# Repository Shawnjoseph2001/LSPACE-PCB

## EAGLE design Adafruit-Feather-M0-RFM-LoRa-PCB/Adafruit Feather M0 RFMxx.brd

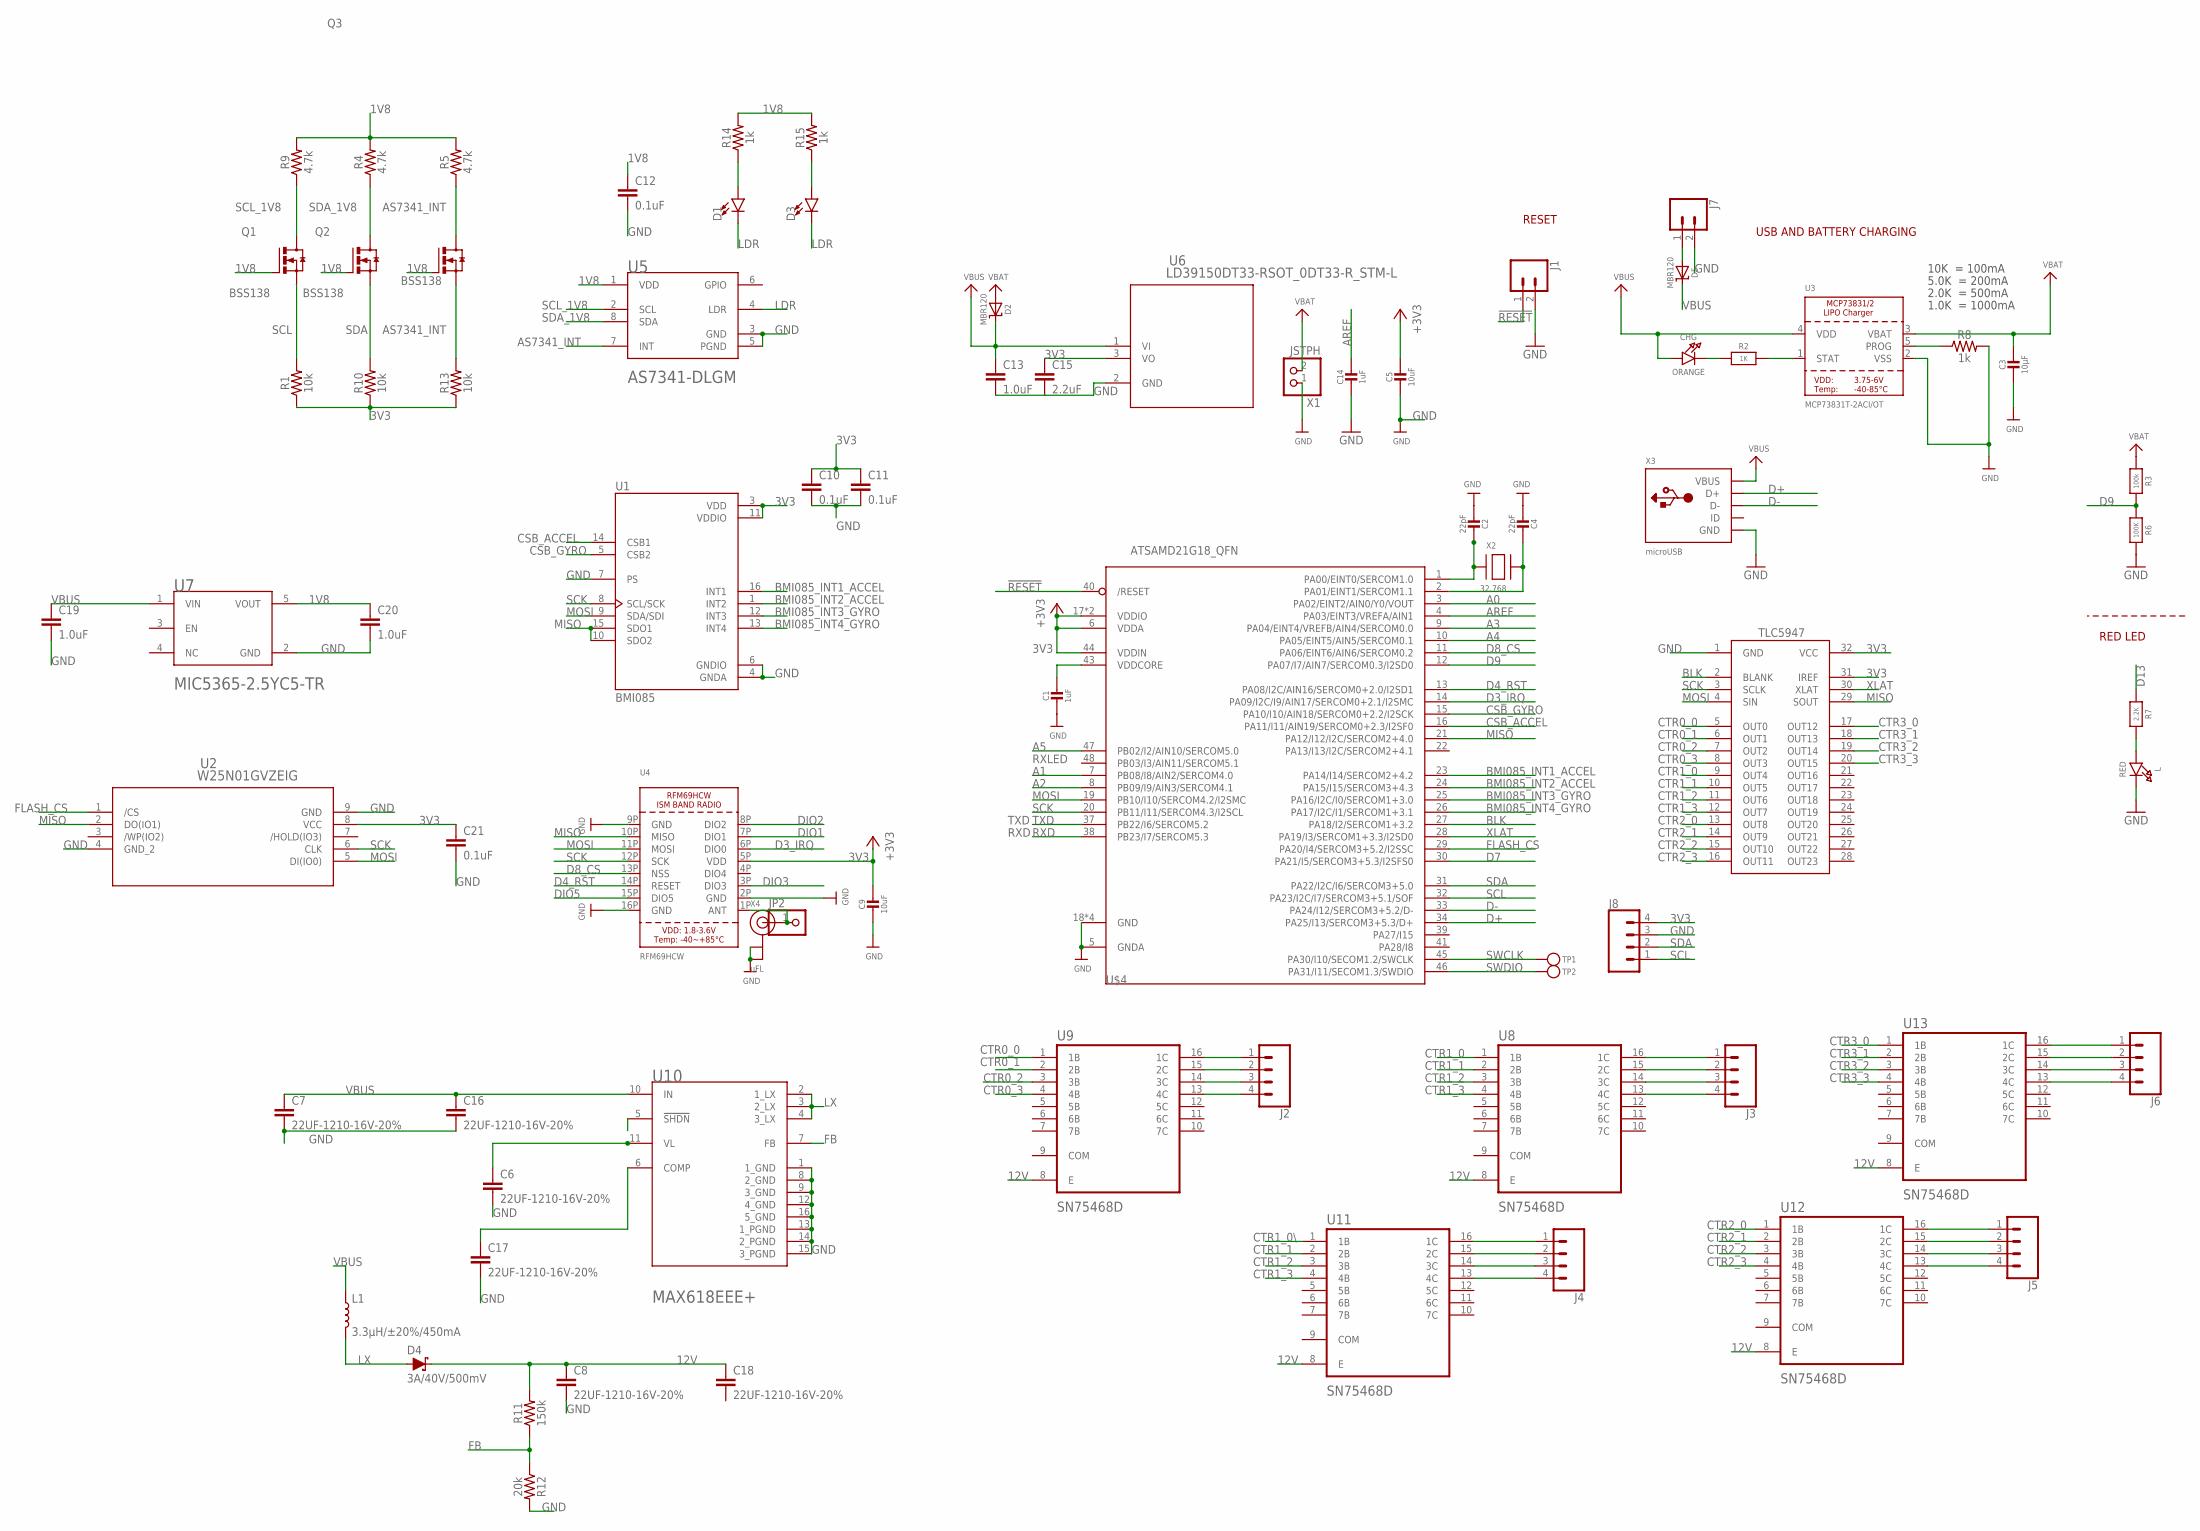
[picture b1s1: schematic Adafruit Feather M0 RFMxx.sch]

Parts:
C1, C14: 1uF; 0603-NO
C2, C4: 22pF; 0603-NO
C3: 10µF; 0805-NO
C5, C9: 10uF; 0805-NO
C6, C7, C8, C16, C17, C18: 22UF-1210-16V-20%; 1210
C10, C11, C12, C21: 0.1uF; 0603
C13, C19, C20: 1.0uF; 0805
C15: 2.2uF; 0805
CHG: ORANGE; CHIPLED_0805_NOOUTLINE
D1, D3: LED1206; LED-1206
D2, D5: MBR120; SOD-123
D4: 3A/40V/500mV; SMA-DIODE
IC1: TLC5947-DAP; HTSSOP32DAP
J1, J7: CONN_02; 1X02
J2, J3, J4, J5, J6, J8: CONN_04; 1X04
JP2: HEADER-1X1ROUND; 1X01_ROUND
L: RED; CHIPLED_0805_NOOUTLINE
L1: 3.3µH/±20%/450mA; 0805
Q1, Q2, Q3: BSS138; SOT23-3
R1, R10, R13: 10k; 0603
R2: 1K; 0603-NO
R3: 100k; 0603-NO
R4, R5, R9: 4.7k; 0603
R6: 100K; 0603-NO
R7: 2.2K; 0603-NO
R8, R14, R15: 1k; 0603
R11: 150k; 0603
R12: 20k; 0603
TP1, TP2: TESTPOINTROUND1.5MM; TESTPOINT_ROUND_1.5MM
U1: BMI085; PQFN50P450X300X100-16N
U2: W25N01GVZEIG; WSON-8_6X5_WIN
U3: MCP73831T-2ACI/OT; SOT23-5
U4: RFM69HCW; RFMHCW_SMT
U5: AMS_AS7341-DLGMAMS_AS7341-DLGM_0_0; AMS_AS7341-DLGM_0
U6: LD39150DT33-RSOT_0DT33-R_STM-L; SOT_0DT33-R_STM-L
U7: MICROCHIP_MIC5365-2_5YC5-TRMICROCHIP_MIC5365-2_5Y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; MICROCHIP_MIC5365-2_5YC5-TR_0
U8, U9, U11, U12, U13: SN75468D; SOIC127P600X175-16N
U10: MAXIM_MAX618EEE+MAXIM_MAX618EEE+_0_0; MAXIM_MAX618EEE+_0
U$4: ATSAMD21G18_QFN; TQFN48_7MM
X1: JSTPH; JSTPH2
X2: 32.768; XTAL3215
X3: microUSB; 4UCONN_20329_V2
X4: uFL; U.FL

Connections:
1V8: C12.1, C20.1, Q1.1 (G), Q2.1 (G), Q3.1 (G), R4.2, R5.2, R9.2, R14.2, R15.2, U5.1 (VDD), U7.5 (VOUT)
3V3: C5.1, C9.1, C10.1, C11.1, C15.1, C21.1, IC1.31 (IREF), IC1.32 (VCC), J8.4, R1.1, R10.1, R13.1, U1.3 (VDD), U1.11 (VDDIO), U2.8 (VCC), U4.5P (VDD), U6.3 (VO), U$4.6 (VDDA), U$4.17 (VDDIO), U$4.36 (VDDIO), U$4.44 (VDDIN)
12V: C8.1, C18.1, D4.C, R11.2, U8.8 (E), U9.8 (E), U11.8 (E), U12.8 (E), U13.8 (E)
!RESET: J1.1, U$4.40 (/RESET)
A0: U$4.3 (PA02/EINT2/AIN0/Y0/VOUT)
A1: U$4.7 (PB08/I8/AIN2/SERCOM4.0)
A2: U$4.8 (PB09/I9/AIN3/SERCOM4.1)
A3: U$4.9 (PA04/EINT4/VREFB/AIN4/SERCOM0.0)
A4: U$4.10 (PA05/EINT5/AIN5/SERCOM0.1)
A5: U$4.47 (PB02/I2/AIN10/SERCOM5.0)
ANT: JP2.1, U4.1P (ANT), X4.3 (SIGNAL)
AREF: C14.1, U$4.4 (PA03/EINT3/VREFA/AIN1)
AS7341_INT: Q3.2 (S), Q3.3 (D), R5.1, R13.2, U5.7 (INT)
BLK: IC1.2 (BLANK), U$4.27 (PA18/I2/SERCOM1+3.2)
BMI085_INT1_ACCEL: U1.16 (INT1), U$4.23 (PA14/I14/SERCOM2+4.2)
BMI085_INT2_ACCEL: U1.1 (INT2), U$4.24 (PA15/I15/SERCOM3+4.3)
BMI085_INT3_GYRO: U1.12 (INT3), U$4.25 (PA16/I2C/I0/SERCOM1+3.0)
BMI085_INT4_GYRO: U1.13 (INT4), U$4.26 (PA17/I2C/I1/SERCOM1+3.1)
CSB_ACCEL: U1.14 (CSB1), U$4.16 (PA11/I11/AIN19/SERCOM0+2.3/I2SF0)
CSB_GYRO: U1.5 (CSB2), U$4.15 (PA10/I10/AIN18/SERCOM0+2.2/I2SCK)
CTR0_0: IC1.5 (OUT0), U9.1 (1B)
CTR0_1: IC1.6 (OUT1), U9.2 (2B)
CTR0_2: IC1.7 (OUT2), U9.3 (3B)
CTR0_3: IC1.8 (OUT3), U9.4 (4B)
CTR1_0: IC1.9 (OUT4), U8.1 (1B)
CTR1_0\: U11.1 (1B)
CTR1_1: IC1.10 (OUT5), U8.2 (2B), U11.2 (2B)
CTR1_2: IC1.11 (OUT6), U8.3 (3B), U11.3 (3B)
CTR1_3: IC1.12 (OUT7), U8.4 (4B), U11.4 (4B)
CTR2_0: IC1.13 (OUT8), U12.1 (1B)
CTR2_1: IC1.14 (OUT9), U12.2 (2B)
CTR2_2: IC1.15 (OUT10), U12.3 (3B)
CTR2_3: IC1.16 (OUT11), U12.4 (4B)
CTR3_0: IC1.17 (OUT12), U13.1 (1B)
CTR3_1: IC1.18 (OUT13), U13.2 (2B)
CTR3_2: IC1.19 (OUT14), U13.3 (3B)
CTR3_3: IC1.20 (OUT15), U13.4 (4B)
D3_IRQ: U4.6P (DIO0), U$4.14 (PA09/I2C/I9/AIN17/SERCOM0+2.1/I2SMC)
D4_RST: U4.14P (RESET), U$4.13 (PA08/I2C/AIN16/SERCOM0+2.0/I2SD1)
D7: U$4.30 (PA21/I5/SERCOM3+5.3/I2SFS0)
D8_CS: U4.13P (NSS), U$4.11 (PA06/EINT6/AIN6/SERCOM0.2)
D9: R3.2, R6.1, U$4.12 (PA07/I7/AIN7/SERCOM0.3/I2SD0)
D13: R7.1
D+: U$4.34 (PA25/I13/SERCOM3+5.3/D+), X3.D+
D-: U$4.33 (PA24/I12/SERCOM3+5.2/D-), X3.D-
DIO1: U4.7P (DIO1)
DIO2: U4.8P (DIO2)
DIO3: U4.3P (DIO3)
DIO5: U4.15P (DIO5)
FB: R11.1, R12.1, U10.7 (FB)
FLASH_CS: U2.1 (/CS), U$4.29 (PA20/I4/SERCOM3+5.2/I2SSC)
GND: C1.2, C2.2, C3.2, C4.2, C5.2, C6.2, C7.2, C8.2, C9.2, C10.2, C11.2, C12.2, C13.2, C14.2, C15.2, C16.2, C17.2, C19.2, C20.2, C21.2, IC1.1 (GND), J1.2, J7.2, J8.3, L.C, R6.2, R8.2, R12.2, U1.4 (GNDA), U1.6 (GNDIO), U1.7 (PS), U2.4 (GND_2), U2.9 (GND), U3.2 (VSS), U4.2P (GND), U4.9P (GND), U4.16P (GND), U5.3 (GND), U5.5 (PGND), U6.2 (GND), U7.2 (GND), U10.1 (1_GND), U10.8 (2_GND), U10.9 (3_GND), U10.12 (4_GND), U10.13 (1_PGND), U10.14 (2_PGND), U10.15 (3_PGND), U10.16 (5_GND), U$4.5 (GNDA), U$4.18 (GND), U$4.35 (GND), U$4.42 (GND), U$4.THERMAL (GND), X1.1, X3.BASE@1 (GND), X3.BASE@2 (GND), X3.GND, X3.SPRT@1 (GND), X3.SPRT@2 (GND), X3.SPRT@3 (GND), X3.SPRT@4 (GND), X4.1 (GND), X4.2 (GND)
LDR: D1.C, D3.C, U5.4 (LDR)
LX: D4.A, L1.2, U10.2 (1_LX), U10.3 (2_LX), U10.4 (3_LX)
MISO: IC1.29 (SOUT), U1.10 (SDO2), U1.15 (SDO1), U2.2 (DO(IO1)), U4.10P (MISO), U$4.21 (PA12/I12/I2C/SERCOM2+4.0)
MOSI: IC1.4 (SIN), U1.9 (SDA/SDI), U2.5 (DI(IO0)), U4.11P (MOSI), U$4.19 (PB10/I10/SERCOM4.2/I2SMC)
unnamed: CHG.C, R2.1
unnamed: L.A, R7.2
unnamed: R2.2, U3.1 (STAT)
unnamed: R8.1, U3.5 (PROG)
unnamed: C2.1, U$4.1 (PA00/EINT0/SERCOM1.0), X2.P$1
unnamed: D1.A, R14.1
unnamed: C4.1, U$4.2 (PA01/EINT1/SERCOM1.1), X2.P$2
unnamed: D3.A, R15.1
unnamed: C6.1, U10.11 (VL)
unnamed: C17.1, U10.6 (COMP)
unnamed: J3.1, U8.16 (1C)
unnamed: J3.2, U8.15 (2C)
unnamed: J3.3, U8.14 (3C)
unnamed: J3.4, U8.13 (4C)
unnamed: J2.1, U9.16 (1C)
unnamed: J2.2, U9.15 (2C)
unnamed: J2.3, U9.14 (3C)
unnamed: J2.4, U9.13 (4C)
unnamed: J4.1, U11.16 (1C)
unnamed: J4.2, U11.15 (2C)
unnamed: J4.3, U11.14 (3C)
unnamed: J4.4, U11.13 (4C)
unnamed: J5.1, U12.16 (1C)
unnamed: J5.2, U12.15 (2C)
unnamed: J5.3, U12.14 (3C)
unnamed: J5.4, U12.13 (4C)
unnamed: J6.1, U13.16 (1C)
unnamed: J6.2, U13.15 (2C)
unnamed: J6.3, U13.14 (3C)
unnamed: J6.4, U13.13 (4C)
unnamed: D5.A, J7.1
RXD: U$4.38 (PB23/I7/SERCOM5.3)
SCK: IC1.3 (SCLK), U1.8 (SCL/SCK), U2.6 (CLK), U4.12P (SCK), U$4.20 (PB11/I11/SERCOM4.3/I2SCL)
SCL: J8.1, Q1.2 (S), R1.2, U$4.32 (PA23/I2C/I7/SERCOM3+5.1/SOF)
SCL_1V8: Q1.3 (D), R9.1, U5.2 (SCL)
SDA: J8.2, Q2.2 (S), R10.2, U$4.31 (PA22/I2C/I6/SERCOM3+5.0)
SDA_1V8: Q2.3 (D), R4.1, U5.8 (SDA)
SWCLK: TP1.P$1, U$4.45 (PA30/I10/SECOM1.2/SWCLK)
SWDIO: TP2.P$1, U$4.46 (PA31/I11/SECOM1.3/SWDIO)
TXD: U$4.37 (PB22/I6/SERCOM5.2)
VBAT: C3.1, D2.A, R3.1, U3.3 (VBAT), X1.2
VBUS: C7.1, C13.1, C16.1, C19.1, CHG.A, D2.C, D5.C, L1.1, U3.4 (VDD), U6.1 (VI), U7.1 (VIN), U10.10 (IN), X3.VBUS
VDDCORE: C1.1, U$4.43 (VDDCORE)
XLAT: IC1.30 (XLAT), U$4.28 (PA19/I3/SERCOM1+3.3/I2SD0)

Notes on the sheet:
RESET
10K = 100mA
5.0K = 200mA
2.0K = 500mA
1.0K = 1000mA
RXLED
TXD
RXD
USB AND BATTERY CHARGING
RED LED

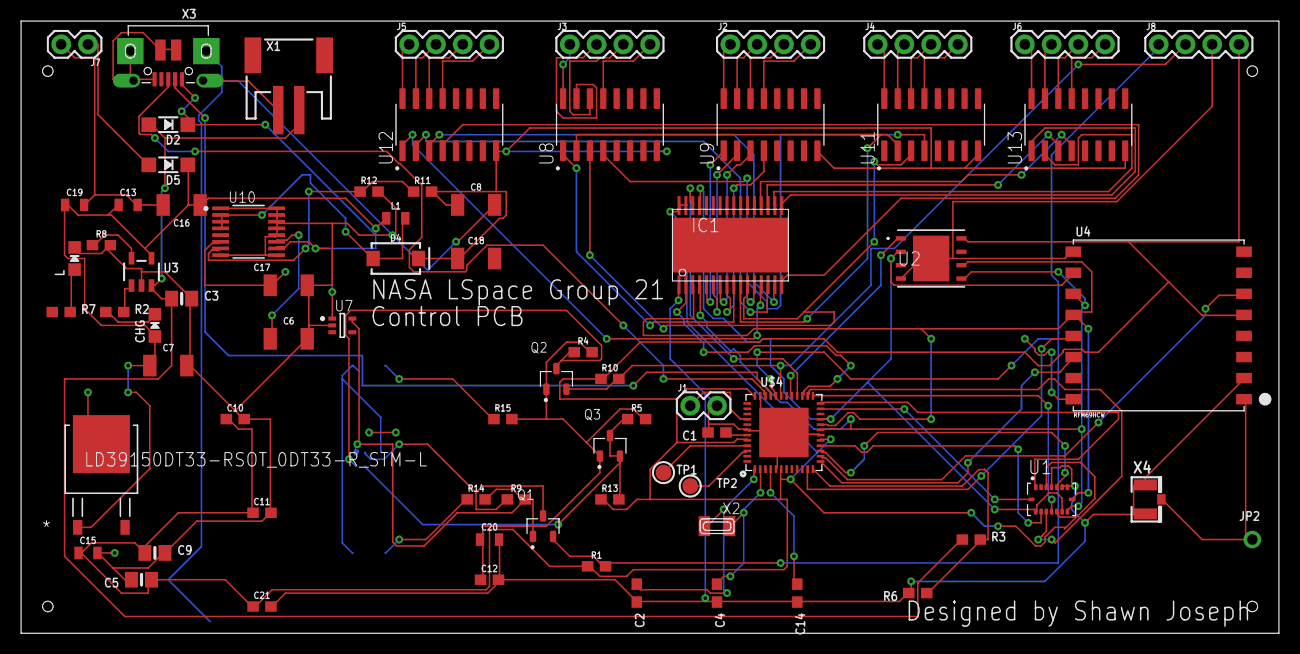
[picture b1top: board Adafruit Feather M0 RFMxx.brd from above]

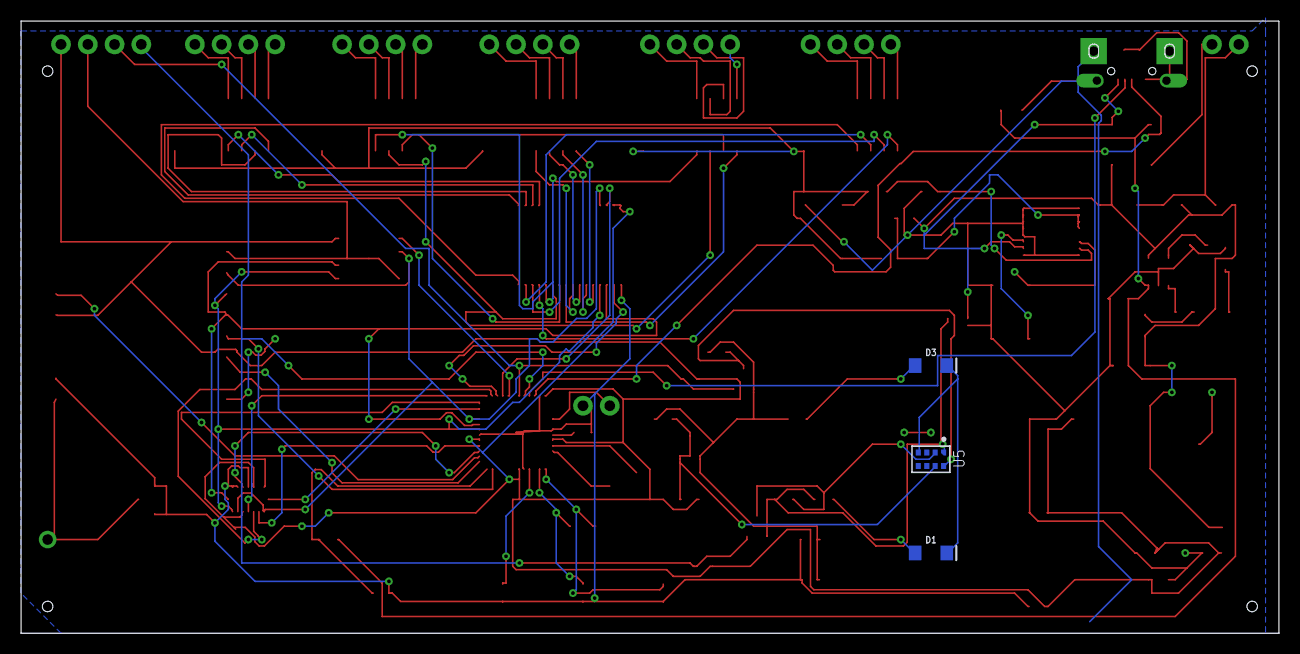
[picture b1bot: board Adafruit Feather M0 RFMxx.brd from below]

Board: 2 copper layers, 119.4 x 58.1 mm, 77 parts (3 on the bottom side), 85 nets.

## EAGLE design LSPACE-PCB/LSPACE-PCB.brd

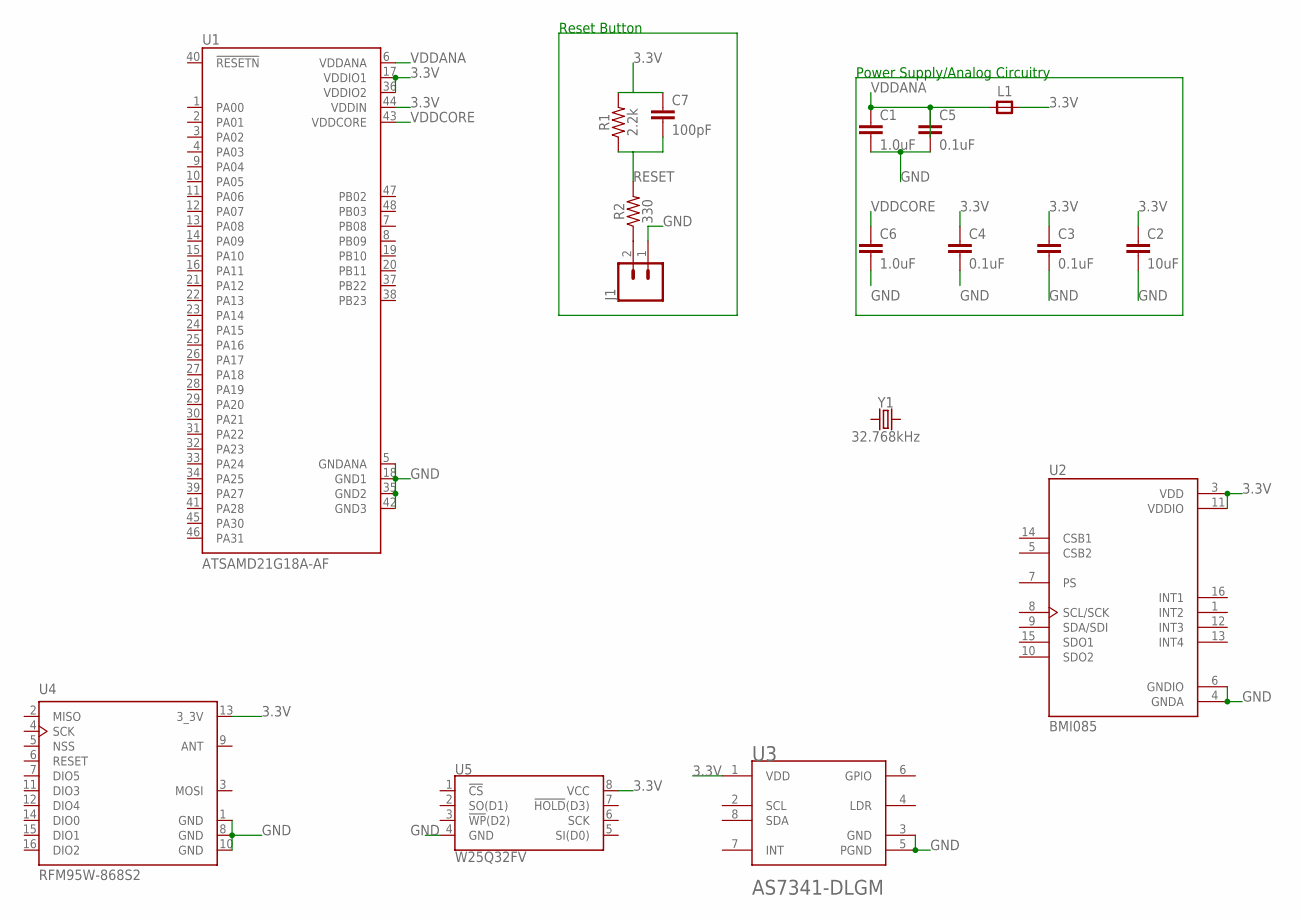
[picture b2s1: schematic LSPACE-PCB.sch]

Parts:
C1, C6: 1.0uF; 1206
C2: 10uF; 1206
C3, C4, C5: 0.1uF; 0603
C7: 100pF; 0603
J1: CONN_02; 1X02
L1: RC-MASTER-SMD_FB_1206MP; RC-MASTER-SMD_L1206MP
R1: 2.2k; 0603
R2: 330; 0603
U1: ATSAMD21G18A-AF; QFP50P900X900X120-48N
U2: BMI085; PQFN50P450X300X100-16N
U3: AMS_AS7341-DLGMAMS_AS7341-DLGM_0_0; AMS_AS7341-DLGM_0
U4: RFM95W-868S2; XCVR_RFM95W-868S2
U5: W25Q32FV; SOIC-8
Y1: 32.768kHz; CRYSTAL-SMD-3.2X1.5MM

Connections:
3.3V: C2.1, C3.1, C4.1, C7.1, L1.2, R1.2, U1.17 (VDDIO1), U1.36 (VDDIO2), U1.44 (VDDIN), U2.3 (VDD), U2.11 (VDDIO), U3.1 (VDD), U4.13 (3_3V), U5.8 (VCC)
GND: C1.2, C2.2, C3.2, C4.2, C5.2, C6.2, J1.1, U1.5 (GNDANA), U1.18 (GND1), U1.35 (GND2), U1.42 (GND3), U2.4 (GNDA), U2.6 (GNDIO), U3.3 (GND), U3.5 (PGND), U4.1 (GND), U4.8 (GND), U4.10 (GND), U5.4 (GND)
unnamed: J1.2, R2.1
RESET: C7.2, R1.1, R2.2
VDDANA: C1.1, C5.1, L1.1, U1.6 (VDDANA)
VDDCORE: C6.1, U1.43 (VDDCORE)

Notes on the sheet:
Reset Button
Power Supply/Analog Circuitry

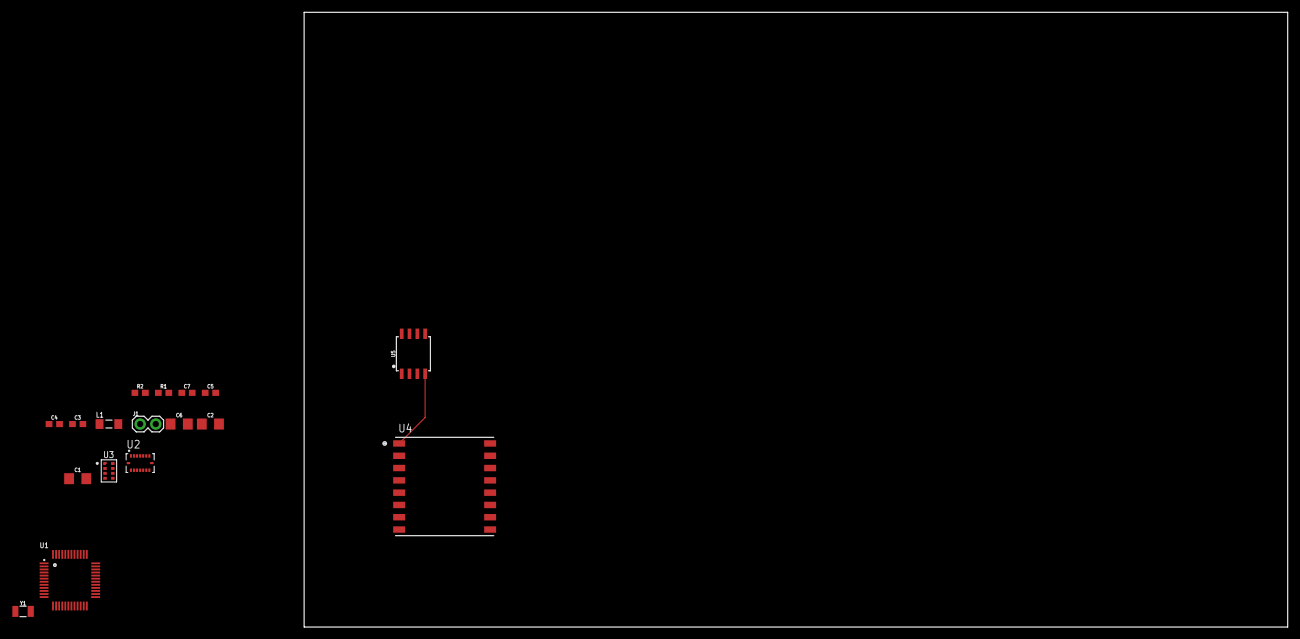
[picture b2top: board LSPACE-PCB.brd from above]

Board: 2 copper layers, 160.0 x 100.0 mm, 17 parts (0 on the bottom side), 6 nets.

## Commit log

2022-03-07 Started initial schematic, added datasheets and Eagle libraries
2022-03-10 Switched to Adafruit based system
2022-03-14 Finished PCB
2022-03-15 Updated files

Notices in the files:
parts and their libraries:
microbuilder: This work is placed in the public domain, and may be freely used for commercial and non-commercial work with the following conditions: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
SparkFun-Capacitors: Licensing: Creative Commons ShareAlike 4.0 International - https://creativecommons.org/licenses/by-sa/4.0
